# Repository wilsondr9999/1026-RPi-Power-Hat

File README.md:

## Introduction
This project is a HAT (hardware attached on top) for the Raspberry Pi, specifically designed for the RatRig V-Core4 3D printer.  This HAT adds some features to the printer that make the electronics wiring easier and more straightforward, and prevent certain problems that can occur with the original RatRig design.

## Features
This HAT does the following:
- Removes the 5V power connection from the Octopus 3D printer control board that was used to power the Raspberry Pi, and replaces it with an on-board, high-current power regulator that can take 24V input directly.  This provides up to 20W (4A of 5V power) to the Raspberry Pi and all of its USB peripherals, rather than relying on the 5V regulator on the Octopus board.
- Provides an additional 4 USB ports to the Raspberry Pi using an on-board USB 2.0 hub IC.  This brings the total number of USB ports available for the 3D printer to 7 instead of 4.  The additional ports can support 2A of current each, with a total of 4A available to be shared among all 7 ports.  The USB hub IC used in this project is the Texas Instruments TUSB8041, a high-quality USB 2.0 hub.
- Includes a small fan that cools the CPU on the Raspberry Pi.  The out-of-the-box design of the V-Core4 has a large fan to cool the entire electronics enclosure, but by default it only runs when the 3D printer's stepper motors are energized.  When they are not, it does not run, and this can cause the Raspberry Pi's temperature to increase into the 60C+ range.  The on-board fan will keep the Pi below 45C when the stepper motors are not running.

## Fabrication
You can have the PCB made at any PCB manufacturer.  The Gerber files are already prepared in the Fabrication Exports folders.  One of the files is [1026 RPi Power Hat](KiCAD%20Project/Fabrication%20Exports%20-%20Oshpark/1026%20RPi%20Power%20Hat.zip) ready for upload to[ Oshpark](https://www.oshpark.com).  The other is [1026 RPi Power Hat](KiCAD%20Project/Fabrication%20Exports%20-%20PCBway/1026%20RPi%20Power%20Hat.kicad_pcb_gerber.zip) ready for upload to [PCBway](https://www.pcbway.com).  If you want to modify the design, the KiCAD project is available in the KiCAD folder.  The PCB is a 4-layer design, your PCB manufacturer needs to support a minimum trace/space of 5 mil (0.127 mm).

For assembly, the recommended method is to use solder paste and a stencil with a reflow oven or hot air station.  The stencil can be made from the [1026 RPi Power Hat-F_Paste](KiCAD%20Project/Fabrication%20Exports/1026%20RPi%20Power%20Hat-F_Paste.gbr) file in the Fabrication Exports folder.  Inexpensive stencils are available from [OshStencils](https://www.oshstencils.com/#).

## Bill of Materials (BOM)
The bill of materials to assemble this project is available in the file [1026 RPi Power Hat](KiCAD%20Project/BOM/1026%20RPi%20Power%20Hat.csv).  Almost all electronic parts are available from Mouser or Digikey.  One exception is the two inductors (L1, L2), these are probably easiest to purchase directly from CoilCraft, the link is in the BOM file.  Some miscellaneous hardware can be purchased from Amazon, those links are also in the BOM file.

## Assembly - Spreading Solder Paste for Reflow
To assemble the unit yourself, you will need a stencil and solder paste, along with a reflow oven or hot air station.  You can obtain the stencil as described above int the Fabrication section.

There is a solder stencil jig that can be 3D printed in the FreeCAD Project folder.  The file [1026 RPi Power Hat SSJ](FreeCAD%20Project/Solder%20Stencil%20Jig%20V2/1026%20RPi%20Power%20Hat%20SSJ.stl) (STL) can be imported into your preferred slicer and printed with the following settings:

- 0.2 mm layer height
- 0.4 mm nozzle
- 15% infill, use the Gyroid pattern
- PLA material

If you use PrusaSlicer, the file [1026 RPi Power Hat SSJ](FreeCAD%20Project/Solder%20Stencil%20Jig%20V2/1026%20RPi%20Power%20Hat%20SSJ.3mf) (3MF) already has these settings.  You may need to adjust the print speeds for your printer, the speeds in the 3MF file are set for a RatRig V-Minion and are quite fast.

If you want to change aspects of the Solder Stencil Jig, the FreeCAD file is available named [Solder Stencil Jig V2](FreeCAD%20Project/Solder%20Stencil%20Jig%20V2/Solder%20Stencil%20Jig%20V2.FCStd), it is a parametric file that can generate a solder stencil jig for any PCB.

Once you have obtained the manufactured PCB, the stencil, and have printed the solder stencil jig, you should have all 3 of them as such:

Insert the PCB into the solder stencil jig, the registration pins will go through the mounting holes:

Clean the PCB surface with isopropyl alcohol (99%), and clean the stencil the same way.  The PCB should look completely clean under a microscope, with no dust, hair, fibers, or oils on the PCB:

Finally, place the stencil on top of the jig, two of the registration pins go through the stencil to align it:

Spread the solder paste onto the stencil using a paste spreader or old plastic card.  Ensure the solder paste fills all openings in the stencil.  Remove the stencil, then carefully pop out the PCB from the jig.  **Do NOT leave the PCB in the jig while placing the components in the next step!**  The components will dislodge from the PCB when you pop it out later.

Your PCB pads should look like this after solder paste is applied:

## Assembly - Placing Components
Begin placing the surface mount components onto the PCB.  Start with the smallest components (0402 surface mount passives -- resistors, capacitors), and work up to the larger components.  Do not place any through-hole components at this stage.  You can place the components with tweezers or use an air-pick tool if available.

You do not need to perfectly align every component, if the component leads are touching the solder paste on the correct pads and the component is flat, you're fine.  When the board is reflowed, the surface tension of the solder paste will pull the components into very good alignment with the pads.

If the solder paste has expanded and is touching adjacent pads like on the USB chip, it probably will not cause an issue.  When the solder melts, the flux and the solder mask on the PCB will direct the liquid solder to the pad and separate the adjacent pins.  After reflow, check carefully for any solder bridges that may remain.

Double- and Triple- check the polarity of the diodes, LEDs, and capacitors when you place them on the PCB, and check the pin 1 marker of all of the chips.  The silkscreen markings on the PCB match the mark on the component (provided you are using the exact component listed in the BOM).

The 0402 LEDs in particular are very difficult to identify which end is the cathode, so carefully check.

Unlike aluminum electrolytic capacitors where the negative terminal is marked, the tantalum polymer capacitors you will be soldering here have the positive terminal marked.  This matches the silkscreen on the PCB.

Once you get to the larger components, you need to carefully look at the pin alignment, especially on the big USB chip.  It is very easy to misalign the chip by one pin in any direction, so double-check it.

Your PCB should look like this after the components are placed:

## Assembly - Reflow
Reflow the PCB in a reflow oven using the solder paste manufacturer's recommended reflow profile.

If you are going to reflow with a hot air station, you need to be extremely careful with the heat level, as some components like the LEDs can melt if the temperature is too high.  Furthermore, the air flow needs to be low, as some of the very small 0402 components can be blown off the PCB.  If you have a PCB preheater, it will be very helpful here.

## Assembly - Through-Hole Components
Solder the through-hole components onto the PCB in the following order:
The following components are on the TOP side of the PCB, so we solder them on from the back side (bottom):
- 2x JST-XH-2 connectors for input power and the fan.  The fan connector is a top-entry, the input power connector is a side-entry.
- 1x USB-B connector for uplink
- 2x USB-A (2 port) connectors for downlink

The following component is on the BOTTOM side of the PCB, so we solder it on from the front side (top):
- 2x20 pin header

Look at the silkscreen marks on the PCB, they identify the side where the component goes.  Then you solder from the other side.

## Cleaning
It is recommended to clean the PCB after soldering to remove all remaining flux.  Isopropyl alcohol will remove it, but may require light brushing with a toothbrush, and may require multiple passes to remove all of the flux.  Use only distilled water or isopropyl alcohol as solvents for cleaning the PCB.  An ultrasonic cleaner with a detergent also works well if available, but **never use Isopropyl alcohol in an ultrasonic cleaner, use distilled water and detergent only.**

If you have used distilled water for rinsing or in an ultrasonic cleaner, dry the PCB using compressed air, and then further dry it in an oven at 125C for 2 hours.

Once you're finished, your PCB should look like this:

## Fan Preparation
The fan that is to be installed on the PCB needs to have the JST-XH-2 connector (part number XHP-2) installed.  Cut the wires on the fan to a length of approximately 2 inches (5 cm), then crimp on two of the JST contacts (part number SXH-001T-P0.6).  Insert the crimped wire/contacts into the XHP-2 connector, pay attention to the required polarity.  The polarity is marked on the PCB, the fan's red wire goes to the positive (+) terminal on the PCB, this is the terminal closest to the M2.5 mounting screw hole.

Use the following picture as a reference for the fan wiring:

Once the fan is terminated, attach it to the PCB using 3x M2.5 16mm hex cap screws and 3 M2.5 hex nuts on the underside of the PCB.  Ensure the fan is oriented correctly such that the air flow is from the top of the PCB through to the bottom of the PCB.  This will blow air onto the Raspberry Pi's CPU that is below.  For maximum effectiveness, add a passive heat sink to the Raspberry Pi's CPU chip.  There are two arrows on the side of the fan that show you both the rotation direction as well as the air flow direction, you can use these to assist you in orienting the fan in the correct position.

## 5V Regulator Heat Sink
There is a square on the bottom side of the PCB that is 6mm x 6mm in size that is bare copper, not covered by solder mask.  This square is directly underneath the 5V regulator and needs to have a small copper heat sink attached to make sure the regulator stays cool.  The heat sink is listed in the BOM .csv file, and is available from Amazon.  Peel off the protective film on the heat sink and press it to the copper square so that it sticks on.  The fan's air flow will also help cool this heat sink.

## Installation into the RatRig V-Core 4
Prepare a 2-wire power lead to go from the 24V power supply in the V-Core4 to the power HAT.  Terminate the ends of the lead on the 24V power supply side using connectors applicable to your power supply.

Terminate the HAT ends of the leads using a JST-XH-2 connector (part number XHP-2) the same way you did the fan.  Crimp on two of the JST contacts (part number SXH-001T-P0.6).  Insert the crimped wire/contacts into the XHP-2 connector, pay attention to the required polarity.  The polarity is marked on the PCB, the negative lead is on the side of the PCB's JST-XH-2 connector that is closest to the M2.5 mounting screw hole.

You will be assembling the HAT onto the top of your Raspberry Pi using 4 brass PCB standoffs (20mm length of the standoff + a 6 mm length of M2.5 threads) and 4 M2.5 x 6mm screws (pan-head phillips).  The BOM .csv file has an Amazon link to a kit that contains these parts.  Use the following photo to see how the HAT is supposed to be mounted on top of the Raspberry Pi:

Mount the HAT to the Raspberry Pi inside the V-Core4's electronics case.  The final result should look like this:

## USB Port Recommendations
Some of the USB devices on the RatRig V-Core4 have higher bandwidth requirements, and/or are more sensitive to issues than others.  Please use the following recommendations for which devices to plug where:

For all V-Core 4 models:
- Plug the USB-A to USB-B cable that connects the Raspberry Pi to the HAT using:
	- 1 USB-A 2.0 port on the Raspberry Pi (black plastic)
	- The USB-B port on the HAT

For CoreXY and Hybrid models:
- Toolhead / EBB42 board: Use a Raspberry Pi 3.0 (blue plastic) port
- Beacon Probe: Use a Raspberry Pi 3.0 (blue plastic) port
- Octopus Board: Use a Raspberry Pi 2.0 (black plastic) port
- Additional accessories, such as a chamber camera, nozzle camera, or touchscreen: Use a USB 2.0 port (black plastic) on the HAT

For IDEX models:
- Toolhead / EBB42 board 0: Use a Raspberry Pi 3.0 (blue plastic) port
- Toolhead / EBB42 board 1: Use the other Raspberry Pi 3.0 (blue plastic) port
- Beacon Probe: Use a Raspberry Pi 2.0 (black plastic) port
- Octopus Board: Use a USB 2.0 (black plastic) port on the HAT
- VAOC Offset Camera: Use a USB 2.0 (black plastic) port on the HAT
- Additional accessories, such as a chamber camera, nozzle camera, or touchscreen: Use a USB 2.0 port (black plastic) on the HAT

Your final installation should look like this:

## Initial Power-Up
At this point, if everything is connected, you can power on the V-Core4.  The HAT will provide the 5V power to the Pi through the GPIO header.  You should see the green power-on LED lit on the HAT.  If you see the red Fault LED lit up on the HAT, check your input voltage, it must be above 22V for the HAT to power on.  If the voltage checks out OK but you still get a fault LED, this may indicate that you have a short on the HAT PCB.  Re-check all soldered connections.

The fault LED can also indicate an overcurrent condition (more than 20W / 4A used by the Pi + fan + all USB devices).  This should be unlikely, but is something to check.  Remove USB devices one at a time, starting with the accessories that are not part of the RatRig V-Core4 systems and see if the fault light goes out.

## Preparing the HAT in Linux
This HAT conforms to the Raspberry Pi HAT+ specification.  The HAT+ specification requires that the HAT contain an EEPROM with information that tells the Raspberry Pi what the HAT is and its capabilities.  We will program this EEPROM and set up the Raspberry PI to recognize it in the next steps.

### Establish a Command Session to your Raspberry Pi
Using an SSH client like [Putty](https://www.putty.org/), connect to your Raspberry Pi using it's IP address on port 22.  The default username and password for the Raspberry Pi, if you have prepared it using RatRig's instructions, is "pi" and "raspberry".  If you have changed these, use your own username and password that you have established.

Once in the command terminal, execute the following commands to prepare the EEPROM:

```
sudo -i
```

The above command will again ask you for the password, the default is "raspberry".

```
apt install cmake
cd /root
git clone https://github.com/raspberrypi/utils.git
cd utils/eeptools
cmake .
make
make install
wget https://github.com/wilsondr9999/1026-RPi-Power-Hat/blob/master/Extras/Linux%20EEPROM%20Preparation/myhat.eep
wget https://github.com/wilsondr9999/1026-RPi-Power-Hat/blob/master/Extras/Linux%20EEPROM%20Preparation/rr-vcore4-powerhat.dtbo
apt install i2c-tools
dtoverlay i2c-gpio i2c_gpio_sda=0 i2c_gpio_scl=1 bus=9
i2cdetect -y 9
```

 The final command above should show you a matrix of detected I2C addresses on the GPIO header.  The HAT is supposed to be detected on address 53, and the number 53 should show up in the matrix.  If it does not, check the HAT for soldering problems.  If it does, proceed with flashing the EEPROM:

```
./eepflash.sh -w -t=24c32 -d=9 -a=53 -f=myhat.eep
```

Make sure the above command completes successfully and does not issue an error message.

```
cp rr-vcore4-powerhat.dtbo /boot/overlays/
sh -c "echo rr-vcore4-powerhat.dtbo >> /boot/config.txt"
```

Now we can reboot the Pi:

```
reboot
```

Once the Pi is rebooted, you can verify that the USB hub is detected and functioning.  Connect to a command session again using your SSH client, and issue the following command:

```
lsusb
```

In the device listing, you should see the HAT's USB hub:

```
Bus 001 Device 005: ID 0451:8142 Texas Instruments, Inc. TUSB8041 4-Port Hub
```

You should also be able to see the RatRig printer devices connected:

```
Bus 001 Device 006: ID 1d50:614e OpenMoko, Inc. stm32f446xx
Bus 001 Device 004: ID 04d8:e72b Microchip Technology, Inc. Beacon RevH
Bus 001 Device 003: ID 1d50:614e OpenMoko, Inc. stm32g0b1xx
Bus 001 Device 002: ID 2109:3431 VIA Labs, Inc. Hub
```

You should also see any additional accessory devices you have added, for example:

```
Bus 001 Device 008: ID 04d9:8030 Holtek Semiconductor, Inc. BTT-HDMI7
Bus 001 Device 007: ID 046d:0825 Logitech, Inc. Webcam C270
```

## Licensing
This project is licensed under two separate licenses:

The hardware design is licensed under the CERN Open Hardware License Version 2 - Weakly Reciprocal.  This copyleft license requires that if you use this device in your product or redistribute this device or its derivatives in any way, that you must:

- Provide the end-users with this license and copyright notice.
- State any changes you have made to the original device, its files, or its documentation.
- Publish your modifications of the device, its files, and its documentation under the same license.
- Indicate to the end-user the original source (this GitHub archive) and that your work is a derivative and/or redistribution.
- The license is "weakly reciprocal" in that it only requires these actions for the modified device itself, not the entire end product that you have incorporated it into.  The rest of the product does not have to follow this license and is not affected by this license.

The documentation, images, and instructions are licensed under the Creative Commons Attribution-ShareAlike 4.0 International Public License.  This copyleft license requires that if you use this device in your product or redistribute this device or its derivatives in any way, that you must:

- Provide the end-users with this license and copyright notice.
- State any changes you have made to the original device, its files, or its documentation.
- Publish your modifications of the device, its files, and its documentation under the same license.
- Indicate to the end-user the original source (this GitHub archive) and that your work is a derivative and/or redistribution.

As stated by the licenses, all uses of this project require attribution and require open-source release under the same licenses.

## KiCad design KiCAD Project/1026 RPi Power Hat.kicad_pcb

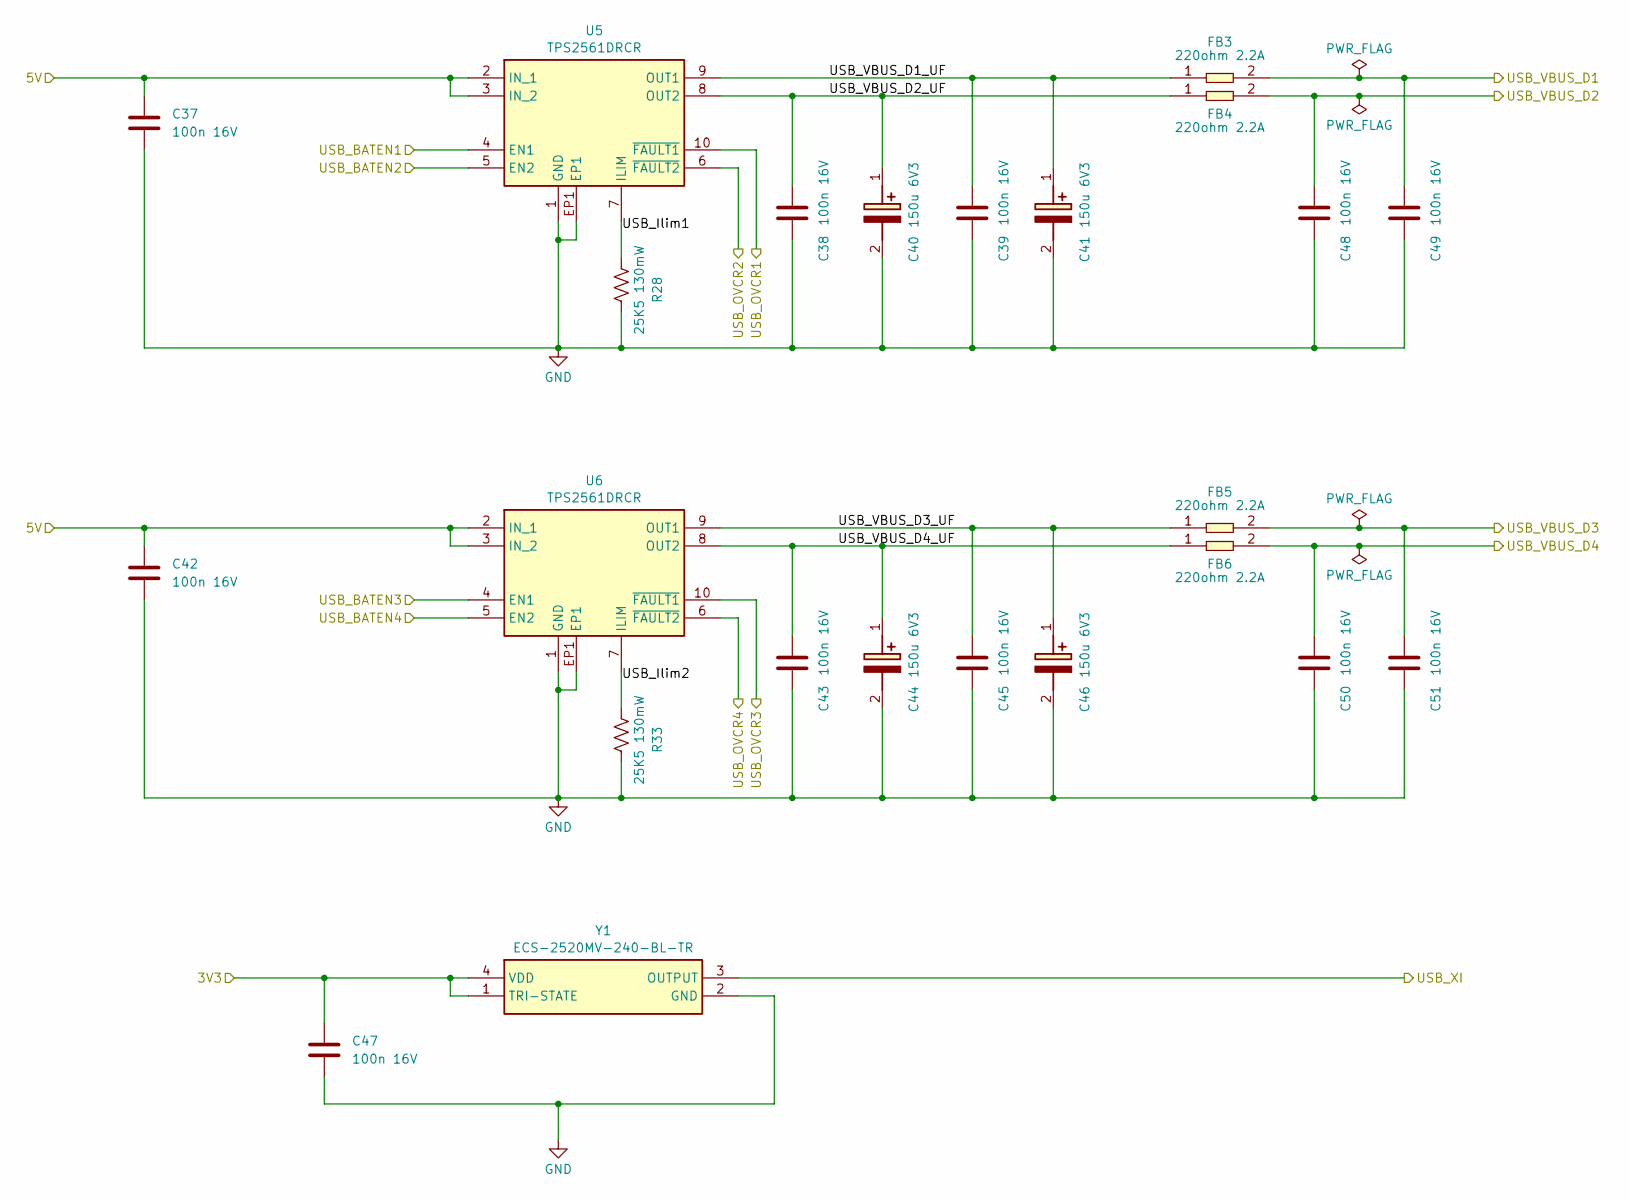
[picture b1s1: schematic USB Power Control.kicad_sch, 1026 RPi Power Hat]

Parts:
C37, C38, C39, C42, C43, C45, C47, C48, C49, C50, C51: GCM155R71C104KA55D; C_0402_1005Metric; Manufacturer_Part_Number GCM155R71C104KA55D; Mouser Part Number 81-GCM155R71C104KA5D
C40, C41, C44, C46: TCJB157M006R0070; [C] Kyocera AVC Tant Poly TCJB157M006R0070; Mouser Part Number 581-TCJB157M006R0070
FB3, FB4, FB5, FB6: BLM18KG221SN1D; [FB] Murata BLM18KG221SN1D 220ohm 2.2A; Mouser Part Number 81-BLM18KG221SN1D
R28, R33: 25K5; R_0402_1005Metric; Manufacturer_Part_Number TNPW040225K5BEED; Mouser Part Number 71-TNPW040225K5BEED
U5, U6: TPS2561DRCR; [U] TI USB Power Ctlr TPS2561DRCR; Mouser Part Number 595-TPS2561DRCR
Y1: ECS-2520MV-240-BL-TR; [Y] ECS Clock Osc 24MHz ECS2520MV240BLTR; Mouser Part Number 520-2520MV-240-BL-TR

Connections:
/5V Regulator/5V: C37.2, C42.2, U5.2 (IN_1), U5.3 (IN_2), U6.2 (IN_1), U6.3 (IN_2); also elsewhere on the board
/Fan / Header / GPIO / EEPROM/3V3: C47.2, Y1.1 (TRI-STATE), Y1.4 (VDD); also elsewhere on the board
/USB ESD Protection/USB_VBUS_D1: C49.2, FB3.2; also elsewhere on the board
/USB ESD Protection/USB_VBUS_D2: C48.2, FB4.2; also elsewhere on the board
/USB ESD Protection/USB_VBUS_D3: C51.2, FB5.2; also elsewhere on the board
/USB ESD Protection/USB_VBUS_D4: C50.2, FB6.2; also elsewhere on the board
/USB Hub/USB_BATEN1: U5.4 (EN1); also elsewhere on the board
/USB Hub/USB_BATEN2: U5.5 (EN2); also elsewhere on the board
/USB Hub/USB_BATEN3: U6.4 (EN1); also elsewhere on the board
/USB Hub/USB_BATEN4: U6.5 (EN2); also elsewhere on the board
/USB Hub/USB_OVCR1: U5.10 (~FAULT1); also elsewhere on the board
/USB Hub/USB_OVCR2: U5.6 (~FAULT2); also elsewhere on the board
/USB Hub/USB_OVCR3: U6.10 (~FAULT1); also elsewhere on the board
/USB Hub/USB_OVCR4: U6.6 (~FAULT2); also elsewhere on the board
/USB Hub/USB_XI: Y1.3 (OUTPUT); also elsewhere on the board
/USB Power Control/USB_Ilim1: R28.1, U5.7 (ILIM)
/USB Power Control/USB_Ilim2: R33.1, U6.7 (ILIM)
/USB Power Control/USB_VBUS_D1_UF: C39.2, C41.1 (+), FB3.1, U5.9 (OUT1)
/USB Power Control/USB_VBUS_D2_UF: C38.2, C40.1 (+), FB4.1, U5.8 (OUT2)
/USB Power Control/USB_VBUS_D3_UF: C45.2, C46.1 (+), FB5.1, U6.9 (OUT1)
/USB Power Control/USB_VBUS_D4_UF: C43.2, C44.1 (+), FB6.1, U6.8 (OUT2)
GND: C37.1, C38.1, C39.1, C40.2 (-), C41.2 (-), C42.1, C43.1, C44.2 (-), C45.1, C46.2 (-), C47.1, C48.1, C49.1, C50.1, C51.1, R28.2, R33.2, U5.1 (GND), U5.EP1, U6.1 (GND), U6.EP1, Y1.2 (GND); also elsewhere on the board

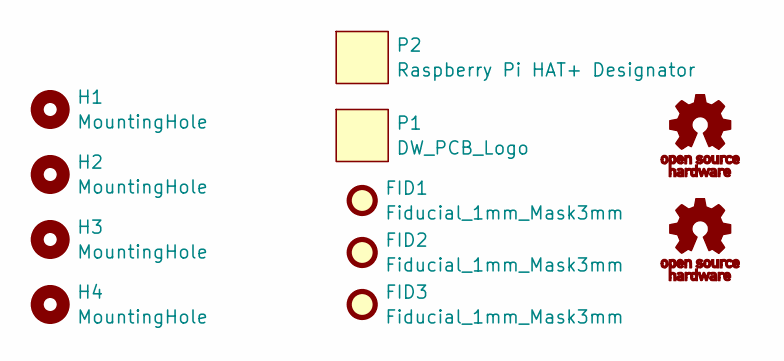
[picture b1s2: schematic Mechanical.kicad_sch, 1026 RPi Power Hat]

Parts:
FID1, FID2, FID3: Fiducial_1mm_Mask3mm; Fiducial_1mm_Mask2mm
G1, G2: OSHW_Logo
H1, H4: MountingHole; [MH] MountingHole_2.7mm_M2.5
H2, H3: MountingHole; [MH] MountingHole_2.7mm_M2.5_StencilRegHole
P1: DW_PCB_Logo
P2: Raspberry Pi HAT+ Designator; [G] RPi HAT+ Designator

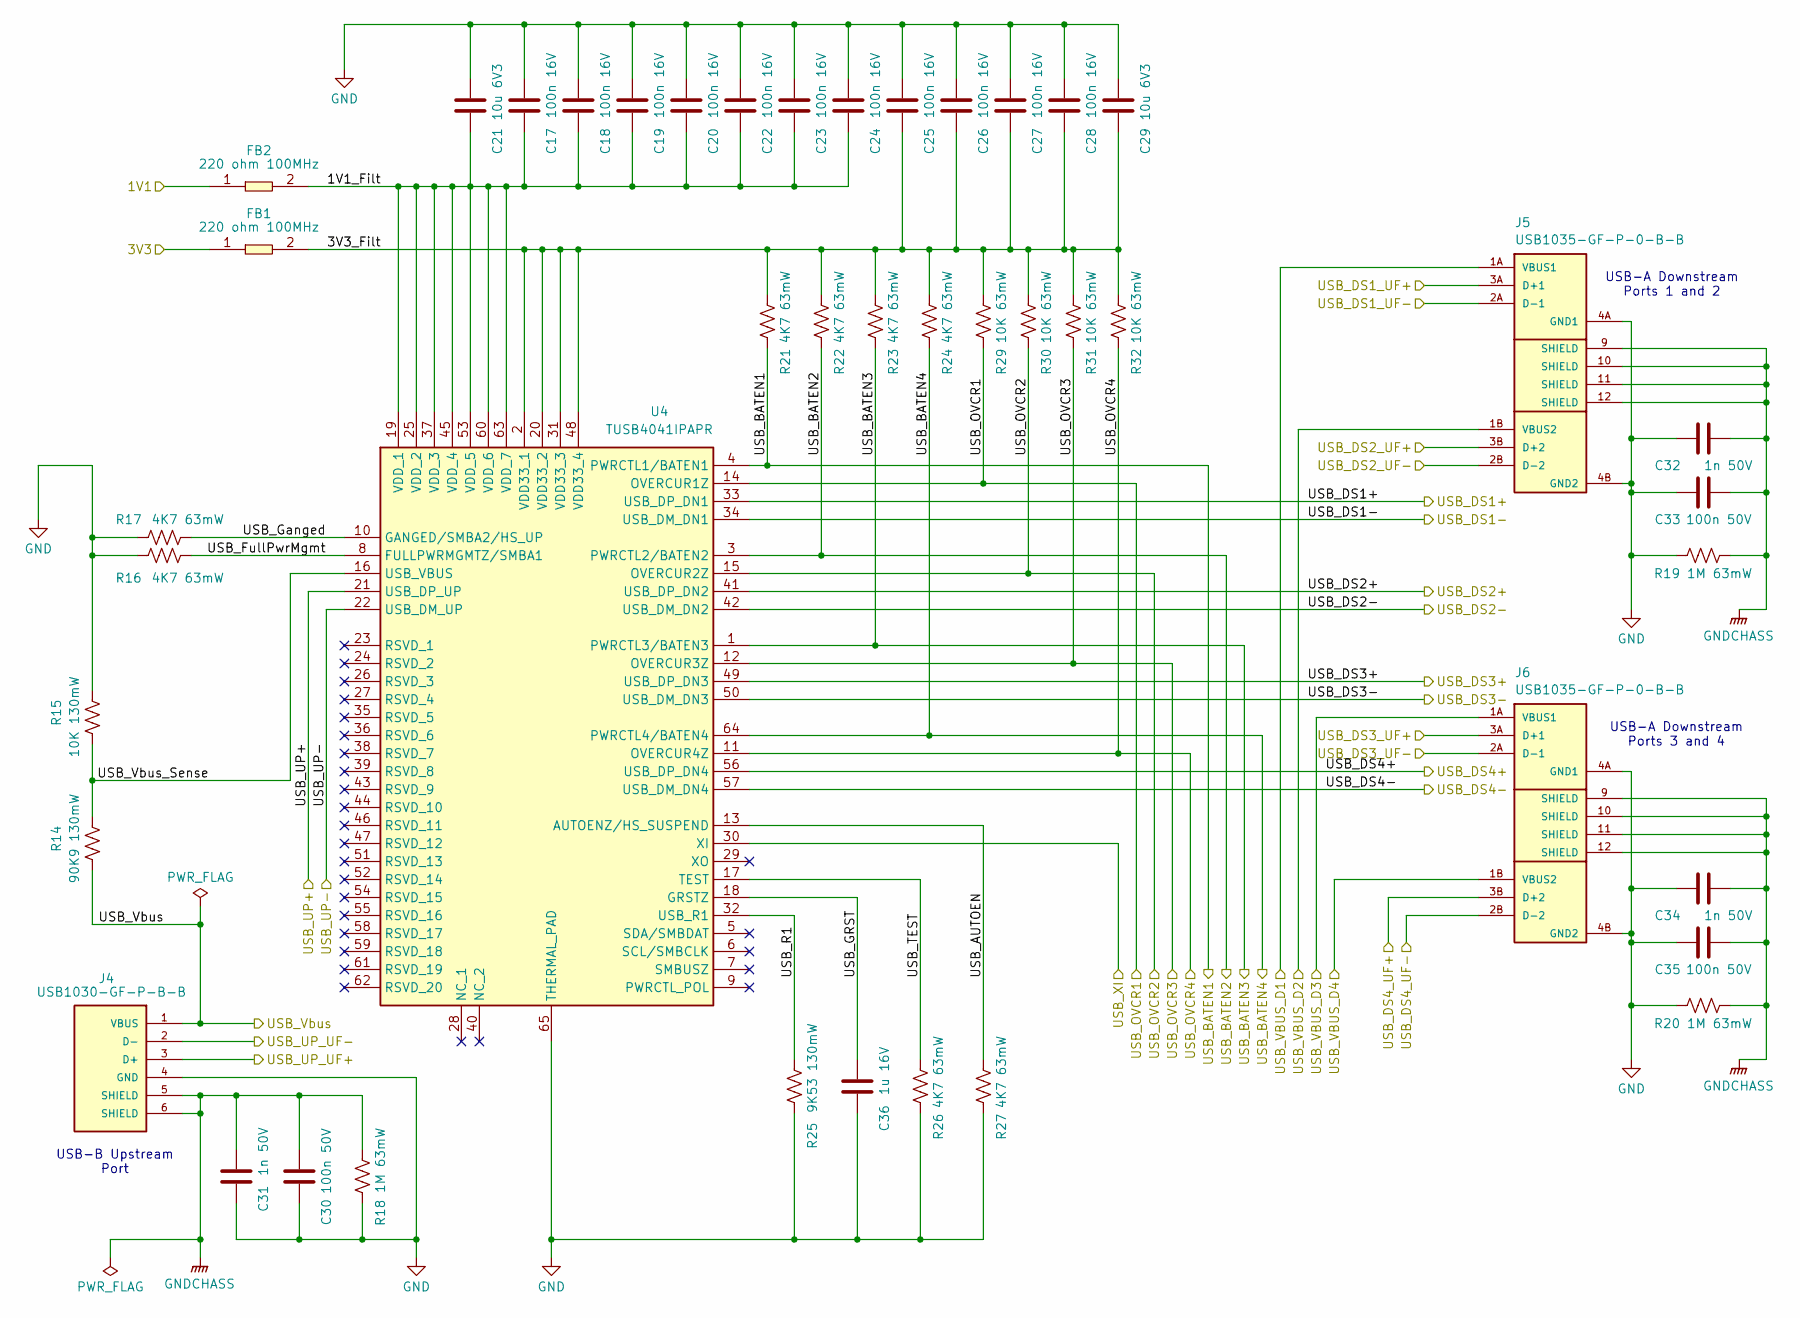
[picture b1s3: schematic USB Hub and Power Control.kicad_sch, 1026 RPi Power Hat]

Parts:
C17, C18, C19, C20, C22, C23, C24, C25, C26, C27, C28: GCM155R71C104KA55D; C_0402_1005Metric; Manufacturer_Part_Number GCM155R71C104KA55D; Mouser Part Number 81-GCM155R71C104KA5D
C21, C29: GCM21BR70J106KE22K; C_0805_2012Metric; Manufacturer_Part_Number GCM21BR70J106KE22K; Mouser Part Number 81-GCM21BR70J106KE2K
C30, C33, C35: GCM155R71H104KE02J; C_0402_1005Metric; Manufacturer_Part_Number GCM155R71H104KE02J; Mouser Part Number 81-GCM155R71H104KE2J
C31, C32, C34: GCM155R71H102KA37D; C_0402_1005Metric; Manufacturer_Part_Number GCM155R71H102KA37D; Mouser Part Number 81-GCM155R71H102KA7D
C36: GCM188R71C105KA64J; C_0603_1608Metric; Manufacturer_Part_Number GCM188R71C105KA64J; Mouser Part Number 81-GCM188R71C105KA4J
FB1, FB2: BLM15PX221SZ1D; [FB] Murata BLM15PX221SZ1D; Mouser Part Number 81-BLM15PX221SZ1D
J4: USB1030-GF-P-B-B; [J] GCT USB-B 2.0 Connector PCB USB1030-GF-P-B-B; Manufacturer_Part_Number USB1030-GF-P-B-B; Mouser Part Number 640-USB1030-GF-P-B-B
J5, J6: USB1035-GF-P-0-B-B; [J] GCT USB-A x2 2.0 Connector USB1035-GF-P-0-B-B; Manufacturer_Part_Number USB1035-GF-P-0-B-B; Mouser Part Number 640-USB1035GFP0BB
R14: 90K9; R_0402_1005Metric; Manufacturer_Part_Number TNPW040290K9BEED; Mouser Part Number 71-TNPW040290K9BEED
R15: 10K; R_0402_1005Metric; Manufacturer_Part_Number TNPW040210K0BEED; Mouser Part Number 71-TNPW040210K0BEED
R16, R17, R21, R22, R23, R24, R26, R27: 4K7; R_0402_1005Metric; Manufacturer_Part_Number CRCW04024K70FKEDC; Mouser Part Number 71-CRCW04024K70FKEDC
R18, R19, R20: 1M; R_0402_1005Metric; Manufacturer_Part_Number CRCW04021M00FKED; Mouser Part Number 71-CRCW0402-1.0M-E3
R25: 9K53; R_0402_1005Metric; Manufacturer_Part_Number TNPW04029K53BEED; Mouser Part Number 71-TNPW04029K53BEED
R29, R30, R31, R32: 10K; R_0402_1005Metric; Manufacturer_Part_Number CRCW040210K0FKEDC; Mouser Part Number 71-CRCW040210K0FKEDC
U4: TUSB4041IPAPR; [U] Texas Inst USB 2.0 Hub Controller TUSB4041I QFP50P1200X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; Mouser Part Number 595-TUSB4041IPAPR

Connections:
/Fan / Header / GPIO / EEPROM/3V3: FB1.1; also elsewhere on the board
/Linear Regulators/1V1: FB2.1; also elsewhere on the board
/USB ESD Protection/USB_DS1_UF+: J5.3A (D+1); also elsewhere on the board
/USB ESD Protection/USB_DS1_UF-: J5.2A (D-1); also elsewhere on the board
/USB ESD Protection/USB_DS2_UF+: J5.3B (D+2); also elsewhere on the board
/USB ESD Protection/USB_DS2_UF-: J5.2B (D-2); also elsewhere on the board
/USB ESD Protection/USB_DS3_UF+: J6.3A (D+1); also elsewhere on the board
/USB ESD Protection/USB_DS3_UF-: J6.2A (D-1); also elsewhere on the board
/USB ESD Protection/USB_DS4_UF+: J6.3B (D+2); also elsewhere on the board
/USB ESD Protection/USB_DS4_UF-: J6.2B (D-2); also elsewhere on the board
/USB ESD Protection/USB_UP_UF+: J4.3 (D+); also elsewhere on the board
/USB ESD Protection/USB_UP_UF-: J4.2 (D-); also elsewhere on the board
/USB ESD Protection/USB_VBUS_D1: J5.1A (VBUS1); also elsewhere on the board
/USB ESD Protection/USB_VBUS_D2: J5.1B (VBUS2); also elsewhere on the board
/USB ESD Protection/USB_VBUS_D3: J6.1A (VBUS1); also elsewhere on the board
/USB ESD Protection/USB_VBUS_D4: J6.1B (VBUS2); also elsewhere on the board
/USB Hub/1V1_Filt: C17.1, C18.1, C19.1, C20.1, C21.2, C22.1, C23.1, C24.1, FB2.2, U4.19 (VDD_1), U4.25 (VDD_2), U4.37 (VDD_3), U4.45 (VDD_4), U4.53 (VDD_5), U4.60 (VDD_6), U4.63 (VDD_7)
/USB Hub/3V3_Filt: C25.1, C26.1, C27.1, C28.1, C29.2, FB1.2, R21.2, R22.2, R23.2, R24.2, R29.2, R30.2, R31.2, R32.2, U4.2 (VDD33_1), U4.20 (VDD33_2), U4.31 (VDD33_3), U4.48 (VDD33_4)
/USB Hub/USB_AUTOEN: R27.2, U4.13 (AUTOENZ/HS_SUSPEND)
/USB Hub/USB_BATEN1: R21.1, U4.4 (PWRCTL1/BATEN1); also elsewhere on the board
/USB Hub/USB_BATEN2: R22.1, U4.3 (PWRCTL2/BATEN2); also elsewhere on the board
/USB Hub/USB_BATEN3: R23.1, U4.1 (PWRCTL3/BATEN3); also elsewhere on the board
/USB Hub/USB_BATEN4: R24.1, U4.64 (PWRCTL4/BATEN4); also elsewhere on the board
/USB Hub/USB_DS1+: U4.33 (USB_DP_DN1); also elsewhere on the board
/USB Hub/USB_DS1-: U4.34 (USB_DM_DN1); also elsewhere on the board
/USB Hub/USB_DS2+: U4.41 (USB_DP_DN2); also elsewhere on the board
/USB Hub/USB_DS2-: U4.42 (USB_DM_DN2); also elsewhere on the board
/USB Hub/USB_DS3+: U4.49 (USB_DP_DN3); also elsewhere on the board
/USB Hub/USB_DS3-: U4.50 (USB_DM_DN3); also elsewhere on the board
/USB Hub/USB_DS4+: U4.56 (USB_DP_DN4); also elsewhere on the board
/USB Hub/USB_DS4-: U4.57 (USB_DM_DN4); also elsewhere on the board
/USB Hub/USB_FullPwrMgmt: R16.2, U4.8 (FULLPWRMGMTZ/SMBA1)
/USB Hub/USB_GRST: C36.1, U4.18 (GRSTZ)
/USB Hub/USB_Ganged: R17.2, U4.10 (GANGED/SMBA2/HS_UP)
/USB Hub/USB_OVCR1: R29.1, U4.14 (OVERCUR1Z); also elsewhere on the board
/USB Hub/USB_OVCR2: R30.1, U4.15 (OVERCUR2Z); also elsewhere on the board
/USB Hub/USB_OVCR3: R31.1, U4.12 (OVERCUR3Z); also elsewhere on the board
/USB Hub/USB_OVCR4: R32.1, U4.11 (OVERCUR4Z); also elsewhere on the board
/USB Hub/USB_R1: R25.2, U4.32 (USB_R1)
/USB Hub/USB_TEST: R26.2, U4.17 (TEST)
/USB Hub/USB_UP+: U4.21 (USB_DP_UP); also elsewhere on the board
/USB Hub/USB_UP-: U4.22 (USB_DM_UP); also elsewhere on the board
/USB Hub/USB_Vbus: J4.1 (VBUS), R14.1; also elsewhere on the board
/USB Hub/USB_Vbus_Sense: R14.2, R15.1, U4.16 (USB_VBUS)
/USB Hub/USB_XI: U4.30 (XI); also elsewhere on the board
GND: C17.2, C18.2, C19.2, C20.2, C21.1, C22.2, C23.2, C24.2, C25.2, C26.2, C27.2, C28.2, C29.1, C30.1, C31.1, C32.1, C33.1, C34.1, C35.1, C36.2, J4.4 (GND), J5.4A (GND1), J5.4B (GND2), J6.4A (GND1), J6.4B (GND2), R15.2, R16.1, R17.1, R18.2, R19.2, R20.2, R25.1, R26.1, R27.1, U4.65 (THERMAL_PAD); also elsewhere on the board
GNDCHASS: C30.2, C31.2, C32.2, C33.2, C34.2, C35.2, J4.5 (SHIELD), J4.6 (SHIELD), J5.9 (SHIELD), J5.10 (SHIELD), J5.11 (SHIELD), J5.12 (SHIELD), J6.9 (SHIELD), J6.10 (SHIELD), J6.11 (SHIELD), J6.12 (SHIELD), R18.1, R19.1, R20.1

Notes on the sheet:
USB-B Upstream Port
USB-A Downstream Ports 1 and 2
USB-A Downstream Ports 3 and 4

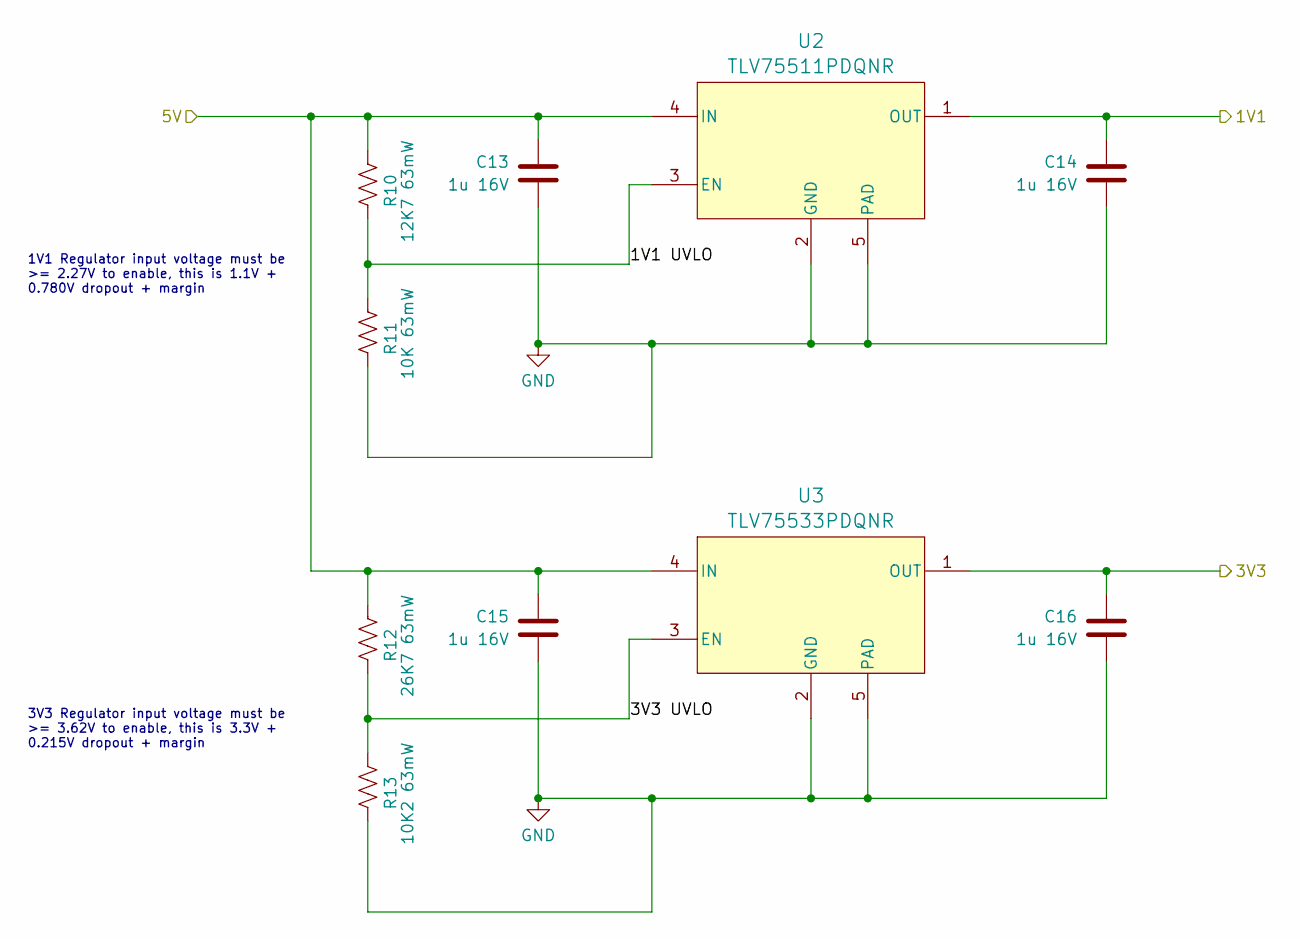
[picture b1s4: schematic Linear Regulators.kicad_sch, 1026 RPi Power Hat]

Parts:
C13, C14, C15, C16: GCM188R71C105KA64J; C_0603_1608Metric; Manufacturer_Part_Number GCM188R71C105KA64J; Mouser Part Number 81-GCM188R71C105KA4J
R10: 12K7; R_0402_1005Metric; Manufacturer_Part_Number CRCW040212K7FKED; Mouser Part Number 71-CRCW0402-12.7K-E3
R11: 10K; R_0402_1005Metric; Manufacturer_Part_Number CRCW040210K0FKEDC; Mouser Part Number 71-CRCW040210K0FKEDC
R12: 26K7; R_0402_1005Metric; Manufacturer_Part_Number CRCW040226K7FKED; Mouser Part Number 71-CRCW0402-26.7K-E3
R13: 10K2; R_0402_1005Metric; Manufacturer_Part_Number CRCW040210K2FKED; Mouser Part Number 71-CRCW0402-10.2K-E3
U2: TLV75511PDQNR; [U] TI LDO Regulator TLV755 DQN; Manufacturer_Part_Number TLV75511PDQNR; Mouser Part Number 595-TLV75511PDQNR
U3: TLV75533PDQNR; [U] TI LDO Regulator TLV755 DQN; Manufacturer_Part_Number TLV75533PDQNR; Mouser Part Number 595-TLV75533PDQNR

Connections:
/5V Regulator/5V: C13.1, C15.1, R10.1, R12.1, U2.4 (IN), U3.4 (IN); also elsewhere on the board
/Fan / Header / GPIO / EEPROM/3V3: C16.1, U3.1 (OUT); also elsewhere on the board
/Linear Regulators/1V1: C14.1, U2.1 (OUT); also elsewhere on the board
/Linear Regulators/1V1 UVLO: R10.2, R11.1, U2.3 (EN)
/Linear Regulators/3V3 UVLO: R12.2, R13.1, U3.3 (EN)
GND: C13.2, C14.2, C15.2, C16.2, R11.2, R13.2, U2.2 (GND), U2.5 (PAD), U3.2 (GND), U3.5 (PAD); also elsewhere on the board

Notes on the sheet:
3V3 Regulator input voltage must be >= 3.62V to enable, this is 3.3V + 0.215V dropout + margin
1V1 Regulator input voltage must be >= 2.27V to enable, this is 1.1V + 0.780V dropout + margin

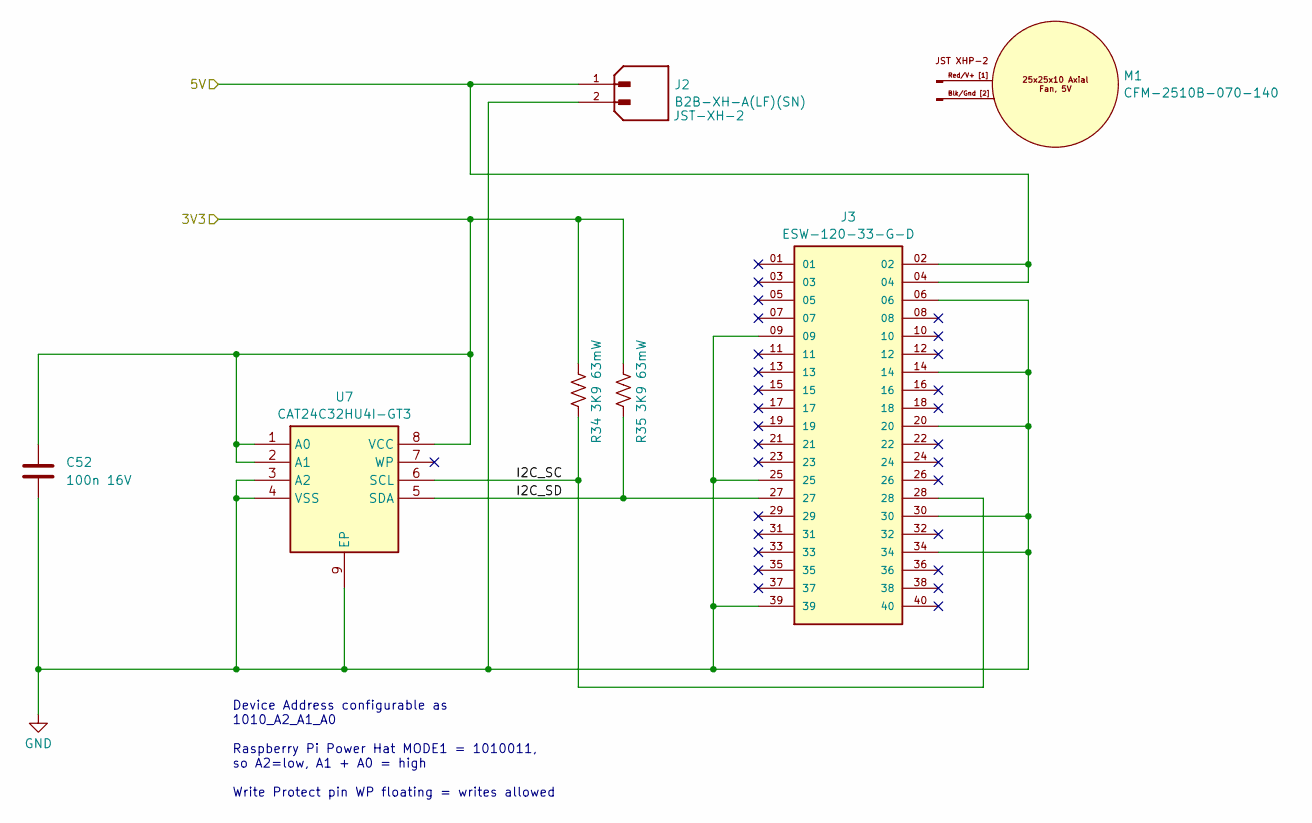
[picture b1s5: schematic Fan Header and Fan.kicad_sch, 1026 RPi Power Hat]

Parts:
C52: GCM155R71C104KA55D; C_0402_1005Metric; Manufacturer_Part_Number GCM155R71C104KA55D; Mouser Part Number 81-GCM155R71C104KA5D
J2: B2B-XH-A(LF)(SN); JST_B2B-XH-A(LF)(SN); Mouser Part Number 306-B2BXHALFSNP; DigiKey_Part_Number 455-B2B-XH-A-ND
J3: ESW-120-33-G-D; [J] Samtec Elevated Socket Strip ESW-120-33-G-D; Manufacturer_Part_Number ESW-120-33-G-D; Mouser Part Number 200-ESW12033GD
M1: CFM-2510B-070-140; [Fan] SameSky CFM-2510B-070-140; Manufacturer_Part_Number CFM-2510B-070-140; Mouser Part Number 490-CFM2510B-070-140
R34, R35: 3K9; R_0402_1005Metric; Manufacturer_Part_Number CRCW04023K90FKED; Mouser Part Number 71-CRCW04023K90FKED
U7: CAT24C32HU4I-GT3; [U] OnSemi Serial EEPROM 4KB CAT24C32HU4I-GT3; Mouser Part Number 863-CAT24C32HU4I-GT3

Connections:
/5V Regulator/5V: J2.1, J3.02, J3.04; also elsewhere on the board
/Fan / Header / GPIO / EEPROM/3V3: C52.2, R34.2, R35.2, U7.1 (A0), U7.2 (A1), U7.8 (VCC); also elsewhere on the board
/Fan / Header / GPIO / EEPROM/I2C_SC: J3.28, R34.1, U7.6 (SCL)
/Fan / Header / GPIO / EEPROM/I2C_SD: J3.27, R35.1, U7.5 (SDA)
GND: C52.1, J2.2, J3.06, J3.09, J3.14, J3.20, J3.25, J3.30, J3.34, J3.39, U7.3 (A2), U7.4 (VSS), U7.9 (EP); also elsewhere on the board

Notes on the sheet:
Device Address configurable as 1010_A2_A1_A0 Raspberry Pi Power Hat MODE1 = 1010011, so A2=low, A1 + A0 = high Write Protect pin WP floating = writes allowed

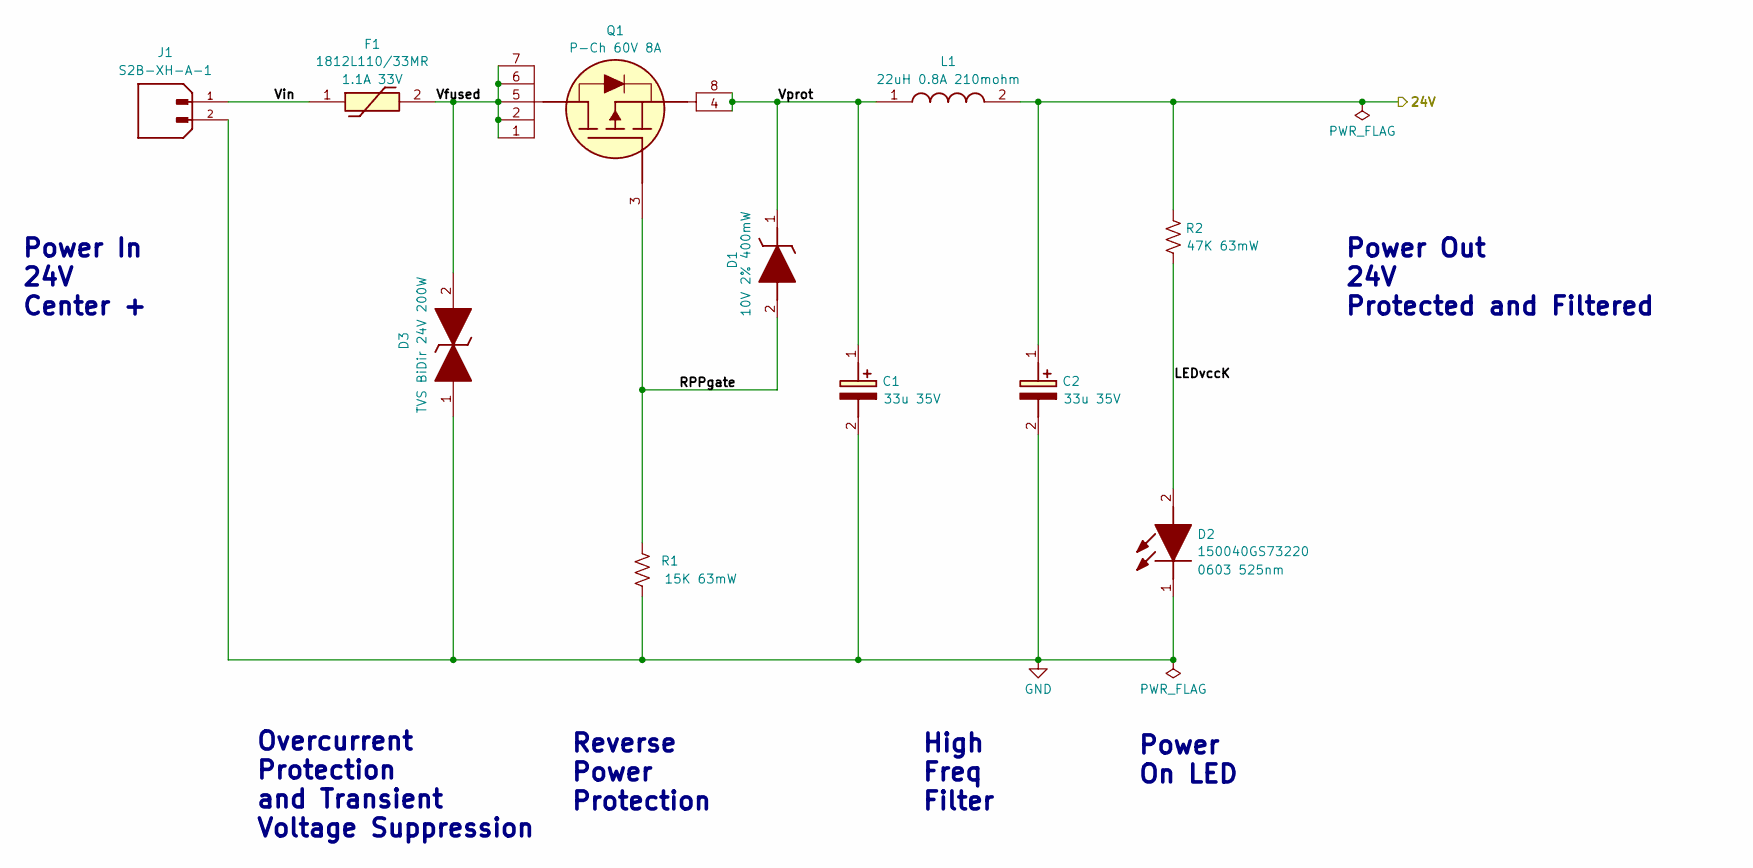
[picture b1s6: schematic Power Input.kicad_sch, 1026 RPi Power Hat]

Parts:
C1, C2: T521D336M035ATE065; [C] Kemet Tantalum Polymer T521X; Mouser Part Number 80-T521D336M35ATE65
D1: PDZ10B,115; [D] Nexperia Zener PDZ10B,115 10V; Mouser Part Number 771-PDZ10B115
D2: 150040GS73220; [D] Wurth Elektronik 150040GS73220; Mouser Part Number 710-150040GS73220
D3: SMF24CA; [D] Littelfuse SMF24CA 24V 200W; Manufacturer_Part_Number SMF24CA; Mouser Part Number 576-SMF24CA
F1: 1812L110/33MR; [F] Littelfuse PPTC 1812L010DR; Mouser Part Number 576-1812L110/33MR
J1: S2B-XH-A-1; [J] JST S2B-XH-A-1; Mouser Part Number 306-S2BXHA1LFSN; DigiKey_Part_Number 455-S2B-XH-A-1-ND
L1: LPS4040-223; [L] Coilcraft Inductor LPS4040; Manufacturer_Part_Number LPS4040-223
Q1: BUK6D120-60PX; [Q] Nexperia BUK6D120-60PX P-Ch 60V 8A; Manufacturer_Part_Number BUK6D120-60PX; Mouser Part Number 771-BUK6D120-60PX
R1: 15K; R_0402_1005Metric; Manufacturer_Part_Number CRCW040215K0FKED; Mouser Part Number 71-CRCW0402-15K-E3
R2: 47K; R_0402_1005Metric; Manufacturer_Part_Number CRCW040247K0FKED; Mouser Part Number 71-CRCW0402-47K-E3

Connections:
/5V Regulator/24V: C2.1 (+), L1.2, R2.1; also elsewhere on the board
/Power Input/LEDvccK: D2.2 (A), R2.2
/Power Input/RPPgate: D1.2 (A), Q1.3 (G), R1.1
/Power Input/Vfused: D3.2, F1.2, Q1.1 (D_1), Q1.2 (D_2), Q1.5 (D_3), Q1.6 (D_4), Q1.7 (D_5)
/Power Input/Vin: F1.1, J1.1
/Power Input/Vprot: C1.1 (+), D1.1 (K), L1.1, Q1.4 (S_1), Q1.8 (S_2)
GND: C1.2 (-), C2.2 (-), D2.1 (K), D3.1, J1.2, R1.2; also elsewhere on the board

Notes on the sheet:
Reverse Power Protection
Power On LED
Overcurrent Protection and Transient Voltage Suppression
High Freq Filter
Power In 24V Center +
Power Out 24V Protected and Filtered

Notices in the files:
KiCAD Project/1026 RPi Power Hat.kicad_pcb:
Copyright © 2025
Copyright © 2025 Dan Wilson
This device's design is licensed under the CERN
Open Hardware License v2, Weakly Reciprocal:
https://ohwr.org/cern_ohl_w_v2.txt
